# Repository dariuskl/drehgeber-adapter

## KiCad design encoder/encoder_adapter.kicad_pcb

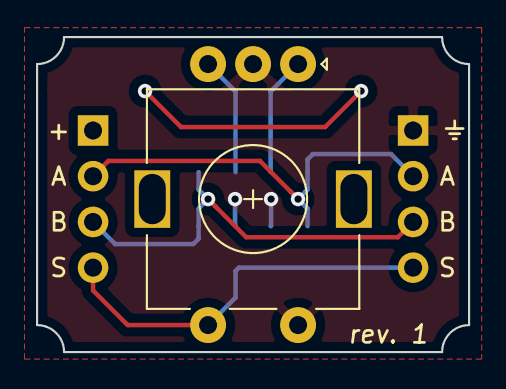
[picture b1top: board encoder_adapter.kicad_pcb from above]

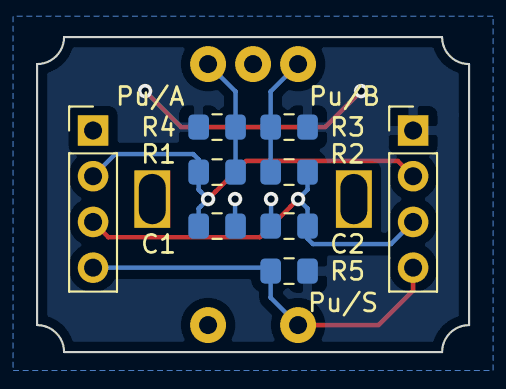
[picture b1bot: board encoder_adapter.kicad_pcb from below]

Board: 2 copper layers, 24.0 x 17.5 mm, 10 parts (9 on the bottom side), 7 nets.

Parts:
C1, C2: 10 nF; C_0805_2012Metric_Pad1.15x1.40mm_HandSolder
R1, R2, R3, R4, R5: 10 k; R_0805_2012Metric_Pad1.15x1.40mm_HandSolder
SW1: Rotary_Encoder_Switch; RotaryEncoder_Alps_EC11E-Switch_Vertical_H20mm
X1, X2: Conn_01x04; PinHeader_1x04_P2.54mm_Vertical

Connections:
A: C1.1, R1.1, X1.2, X2.2
B: C2.1, R2.1, X1.3, X2.3
GND: C1.2, C2.2, SW1.C, SW1.S2, X2.1
unnamed: R1.2, R4.2, SW1.A
unnamed: R2.2, R3.2, SW1.B
S: R5.2, SW1.S1, X1.4, X2.4
VDD: R3.1, R4.1, R5.1, X1.1

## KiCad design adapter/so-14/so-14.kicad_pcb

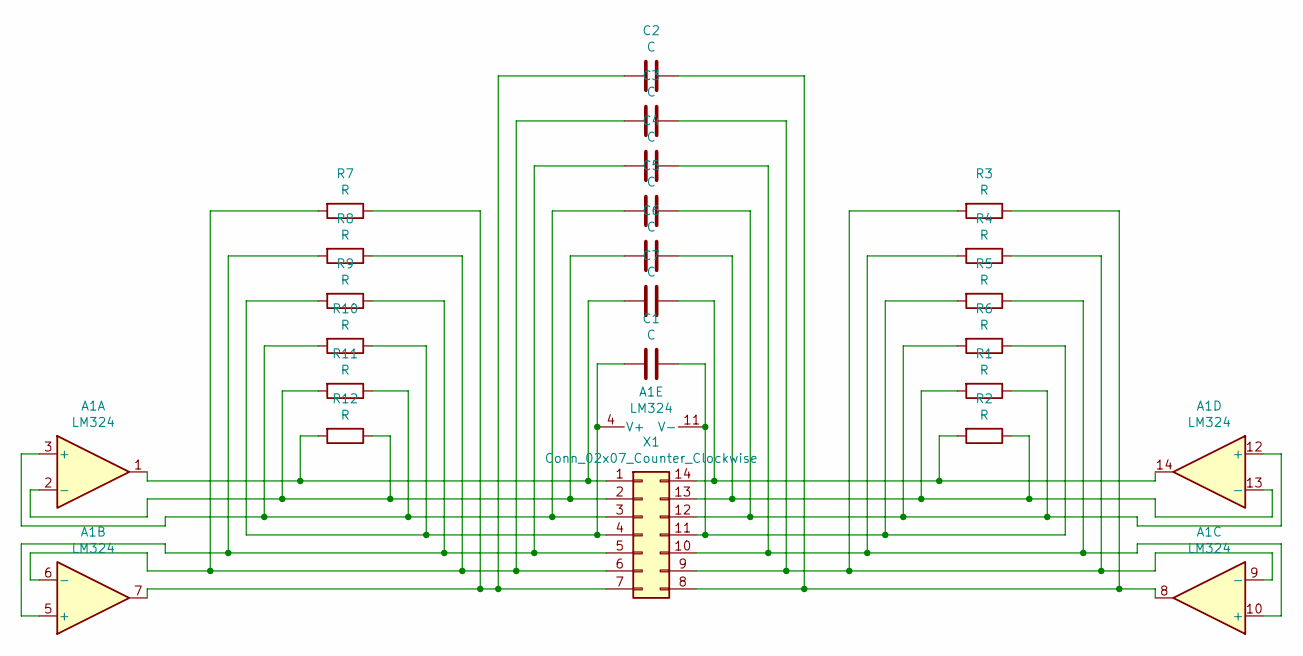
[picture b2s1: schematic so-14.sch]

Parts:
A1: LM324; SOIC-14_3.9x8.7mm_P1.27mm
C1, C2, C3, C4, C5, C6, C7: C; C_0805_2012Metric_Pad1.15x1.40mm_HandSolder
R1, R2, R3, R4, R5, R6, R7, R8, R9, R10, R11, R12: R; R_0805_2012Metric_Pad1.15x1.40mm_HandSolder
X1: Conn_02x07_Counter_Clockwise; DIP-14_W10.16mm

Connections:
unnamed: A1.1, C7.2, R12.2, X1.1
unnamed: A1.2 (-), C6.2, R11.2, R12.1, X1.2
unnamed: A1.3 (+), C5.2, R10.2, R11.1, X1.3
unnamed: A1.4 (V+), C1.2, R9.2, R10.1, X1.4
unnamed: A1.5 (+), C4.2, R8.2, R9.1, X1.5
unnamed: A1.6 (-), C3.2, R7.2, R8.1, X1.6
unnamed: A1.7, C2.2, R7.1, X1.7
unnamed: A1.8, C2.1, R3.1, X1.8
unnamed: A1.9 (-), C3.1, R3.2, R4.1, X1.9
unnamed: A1.10 (+), C4.1, R4.2, R5.1, X1.10
unnamed: A1.11 (V-), C1.1, R5.2, R6.1, X1.11
unnamed: A1.12 (+), C5.1, R1.1, R6.2, X1.12
unnamed: A1.13 (-), C6.1, R1.2, R2.1, X1.13
unnamed: A1.14, C7.1, R2.2, X1.14

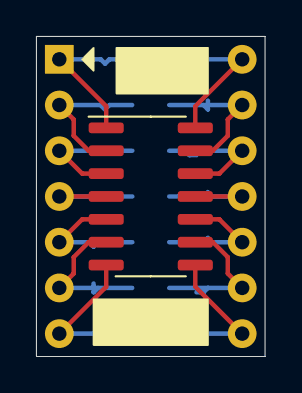
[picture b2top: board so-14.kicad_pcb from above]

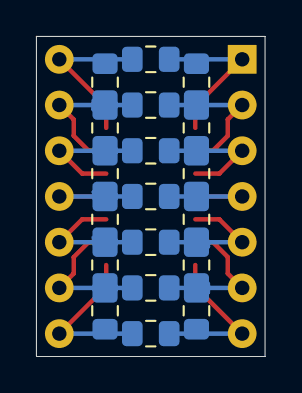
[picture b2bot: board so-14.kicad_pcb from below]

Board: 2 copper layers, 12.7 x 17.8 mm, 21 parts (19 on the bottom side), 14 nets.

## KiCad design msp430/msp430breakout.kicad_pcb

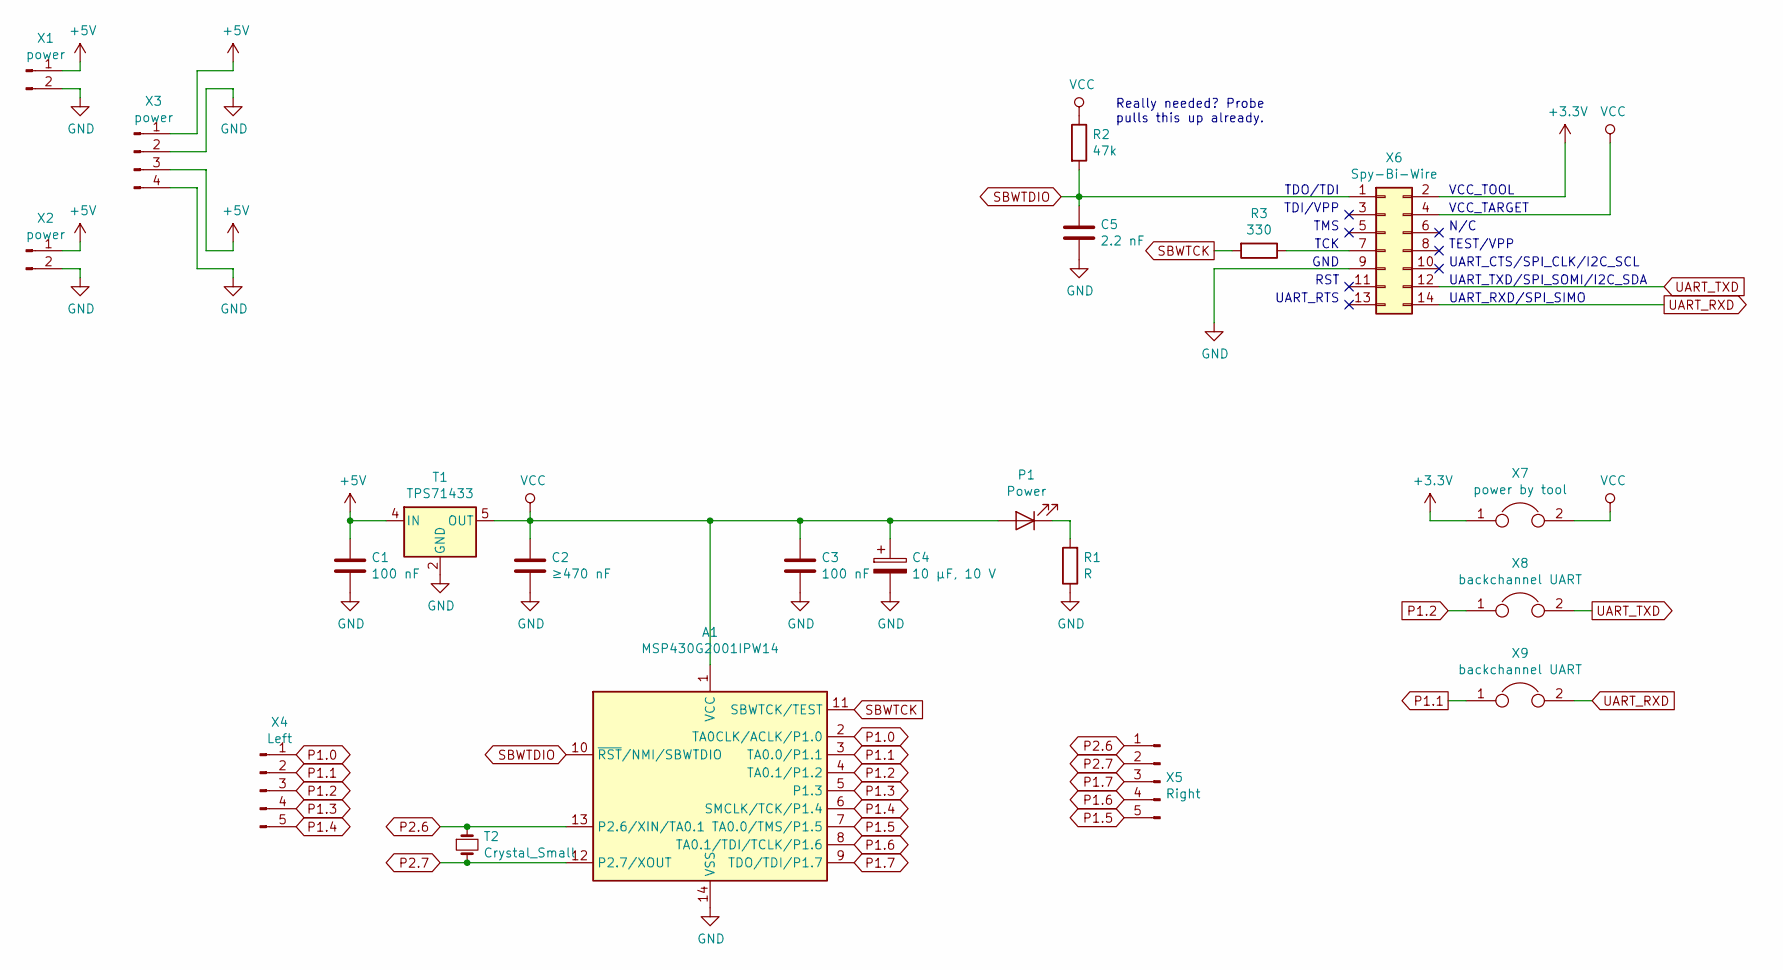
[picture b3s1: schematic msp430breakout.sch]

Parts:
A1: MSP430G2001IPW14; TSSOP-14_4.4x5mm_P0.65mm
C1, C3: 100 nF; C_0805_2012Metric_Pad1.15x1.40mm_HandSolder
C2: ≥470 nF; C_0805_2012Metric_Pad1.15x1.40mm_HandSolder
C4: 10 µF, 10 V; CP_EIA-3528-21_Kemet-B_Pad1.50x2.35mm_HandSolder
C5: 2.2 nF; C_0805_2012Metric_Pad1.15x1.40mm_HandSolder
P1: Power; LED_0805_2012Metric_Pad1.15x1.40mm_HandSolder
R1: R; R_0805_2012Metric_Pad1.15x1.40mm_HandSolder
R2: 47k; R_0805_2012Metric_Pad1.15x1.40mm_HandSolder
R3: 330; R_0805_2012Metric_Pad1.15x1.40mm_HandSolder
T1: TPS71433; SOT-353_SC-70-5
T2: Crystal_Small
X1, X2: power; PinHeader_1x02_P2.54mm_Vertical
X3: power; PinHeader_2x02_P2.54mm_Vertical
X4: Left; PinHeader_1x05_P2.54mm_Vertical
X5: Right; PinHeader_1x05_P2.54mm_Vertical
X6: Spy-Bi-Wire; IDC-Header_2x07_P2.54mm_Vertical
X7: power by tool; PinHeader_1x02_P2.54mm_Vertical
X8, X9: backchannel UART; R_0805_2012Metric_Pad1.15x1.40mm_HandSolder

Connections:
+3V3: X6.2, X7.1
+5V: C1.1, T1.4 (IN), X1.1, X2.1, X3.1, X3.3
GND: A1.14 (VSS), C1.2, C2.2, C3.2, C4.2, C5.2, R1.1, T1.2 (GND), X1.2, X2.2, X3.2, X3.4, X6.9
unnamed: P1.1 (K), R1.2
unnamed: R3.1, X6.7
P1.0: A1.2 (TA0CLK/ACLK/P1.0), X4.1
P1.1: A1.3 (TA0.0/P1.1), X4.2, X9.1
P1.2: A1.4 (TA0.1/P1.2), X4.3, X8.1
P1.3: A1.5 (P1.3), X4.4
P1.4: A1.6 (SMCLK/TCK/P1.4), X4.5
P1.5: A1.7 (TA0.0/TMS/P1.5), X5.5
P1.6: A1.8 (TA0.1/TDI/TCLK/P1.6), X5.4
P1.7: A1.9 (TDO/TDI/P1.7), X5.3
P2.6: A1.13 (P2.6/XIN/TA0.1), T2.1, X5.1
P2.7: A1.12 (P2.7/XOUT), T2.2, X5.2
SBWTCK: A1.11 (SBWTCK/TEST), R3.2
SBWTDIO: A1.10 (~RST~/NMI/SBWTDIO), C5.1, R2.2, X6.1
UART_RXD: X6.14, X9.2
UART_TXD: X6.12, X8.2
VCC: A1.1 (VCC), C2.1, C3.1, C4.1, P1.2 (A), R2.1, T1.5 (OUT), X6.4, X7.2

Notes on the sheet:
VCC_TOOL
VCC_TARGET
TDO/TDI
TDI/VPP
TMS
Really needed? Probe pulls this up already.
TEST/VPP
N/C
TCK
GND
RST
UART_RTS
UART_CTS/SPI_CLK/I2C_SCL
UART_TXD/SPI_SOMI/I2C_SDA
UART_RXD/SPI_SIMO

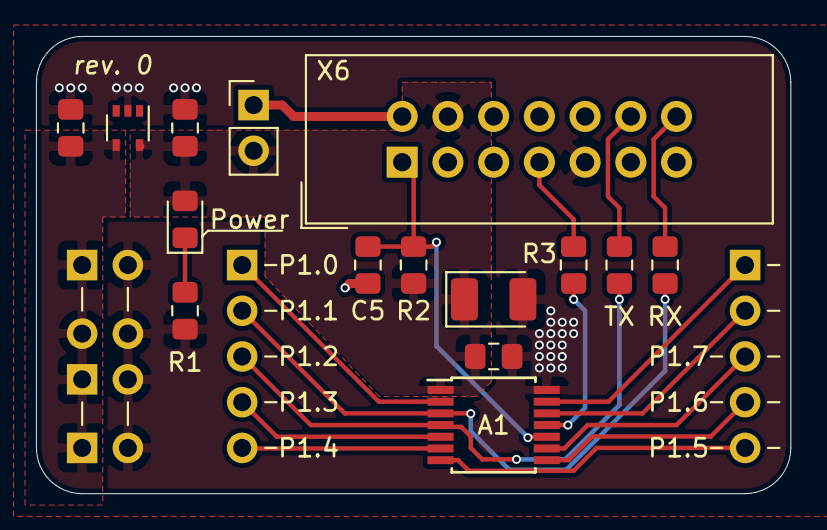
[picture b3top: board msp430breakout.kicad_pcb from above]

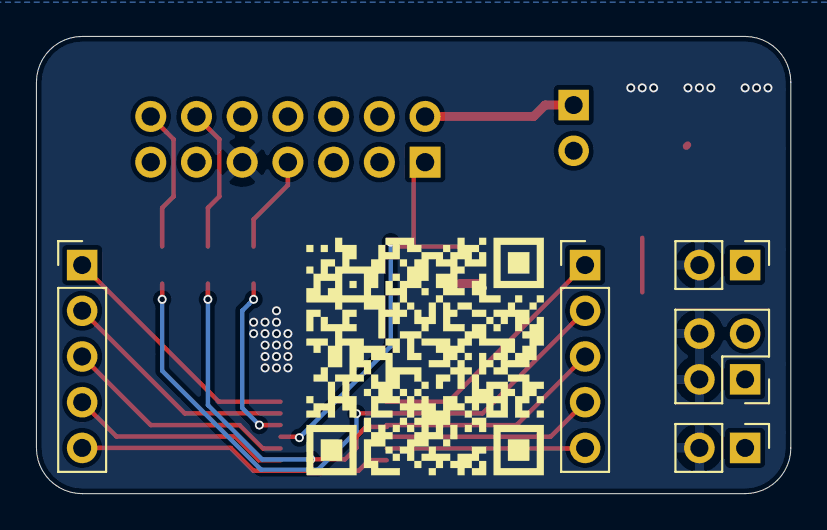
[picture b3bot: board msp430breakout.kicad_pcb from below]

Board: 2 copper layers, 41.9 x 25.4 mm, 21 parts (6 on the bottom side), 20 nets.

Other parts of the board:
QR*****: QR_AISLER

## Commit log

2020-02-20 start work on second board (MSP430 breakout)
2020-02-20 a bit of work on the layout
2020-02-21 increased board size to have planes go around pin headers
2020-02-21 started work on example drivers for encoders
2020-02-21 added linear regulator
2020-02-26 added SO-8 adapter board
2020-02-29 modified for better usability with FET
2020-03-07 finished rev.0
2020-05-03 added so-14 THT adapter
2020-08-15 fixed VCC not connecting to A
2020-08-16 set revision to 1
2020-12-09 comitting current state
